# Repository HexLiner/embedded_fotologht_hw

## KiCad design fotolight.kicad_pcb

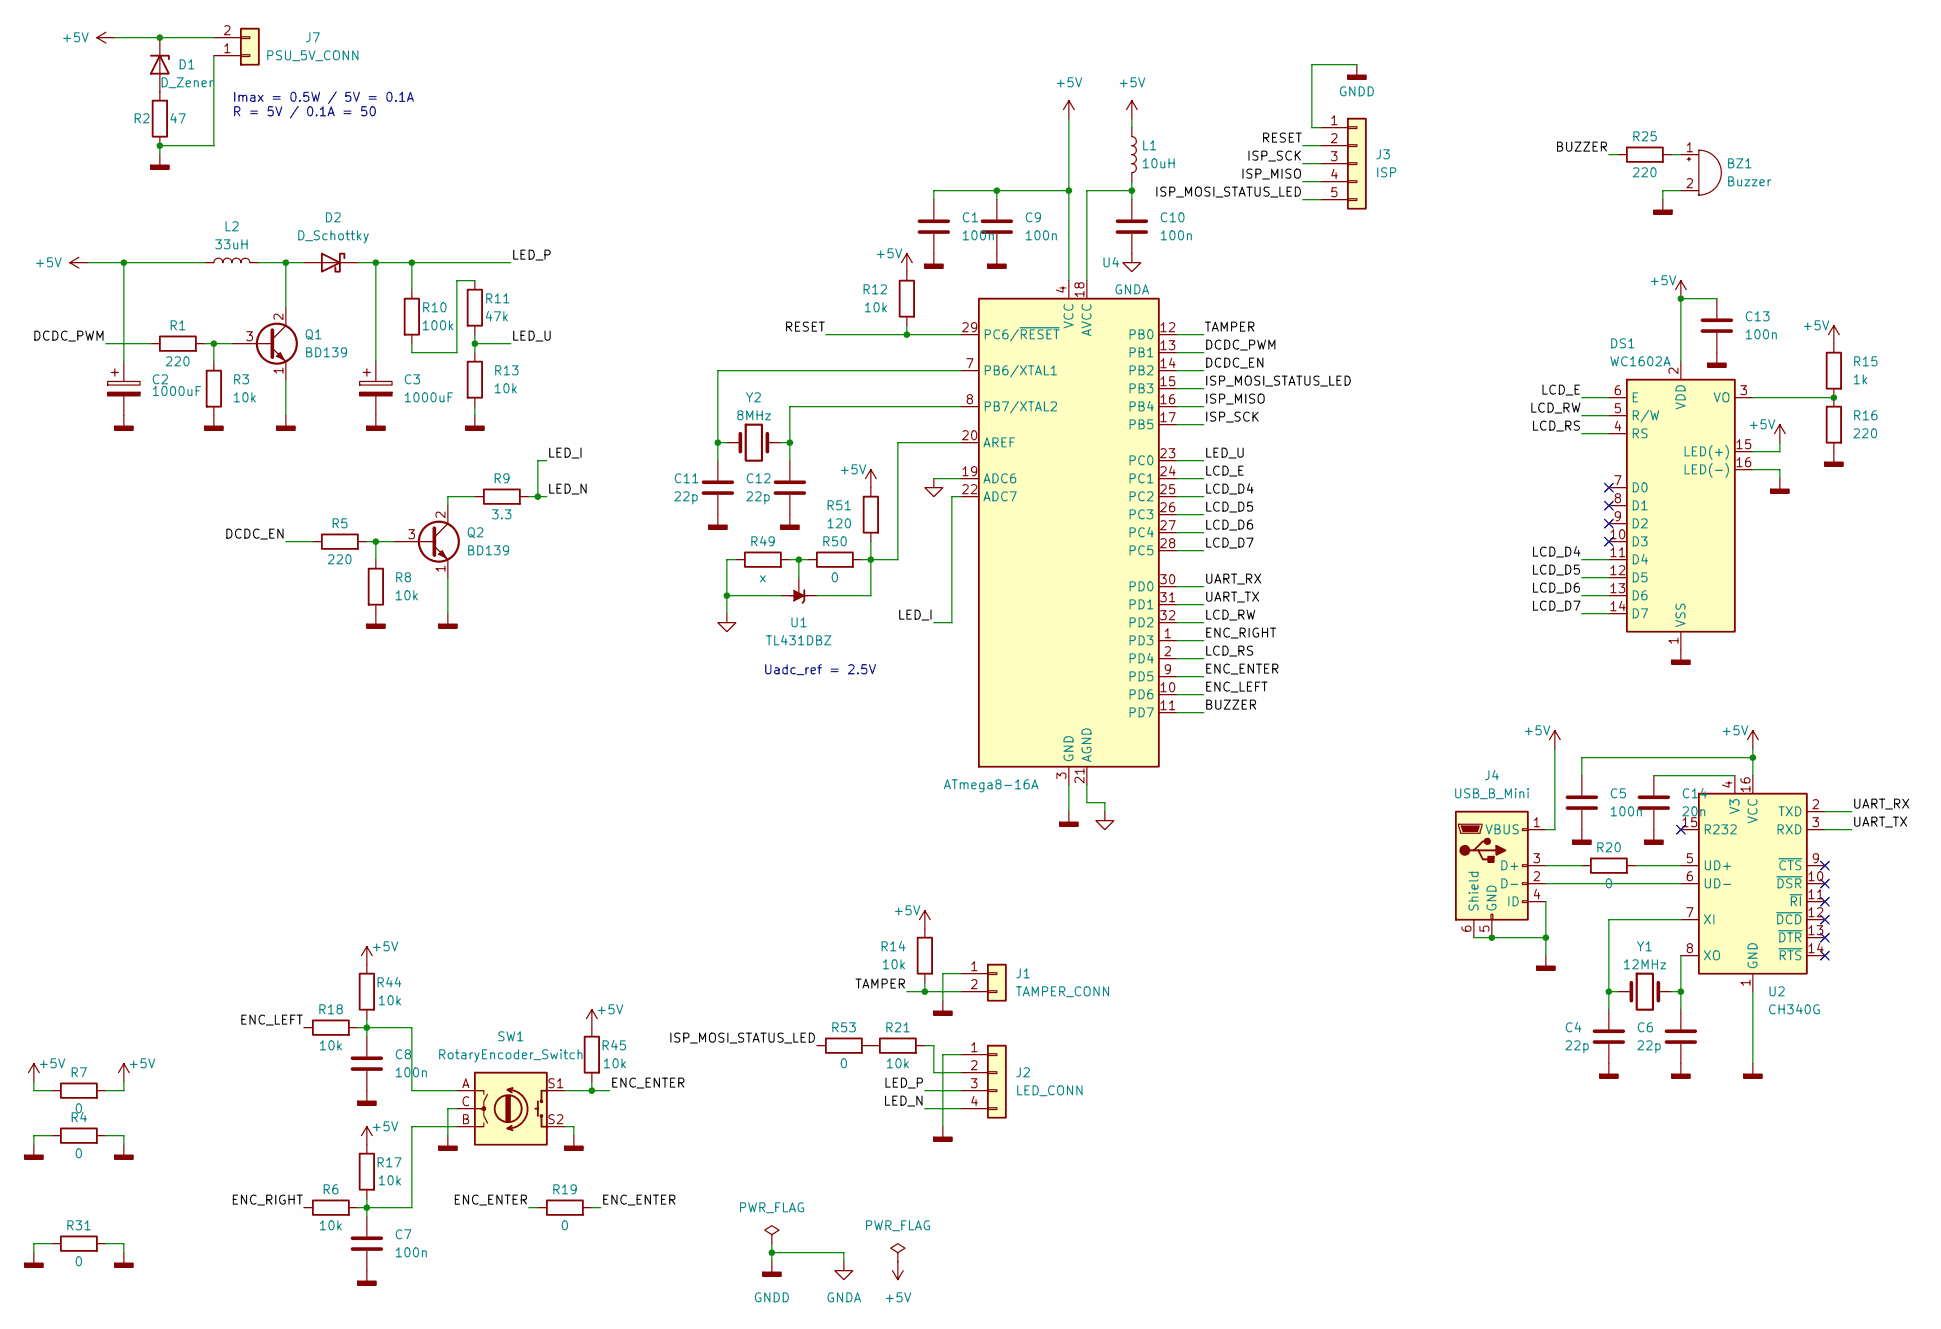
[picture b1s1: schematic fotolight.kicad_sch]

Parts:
BZ1: Buzzer; Buzzer_12x9.5RM7.6
C1, C5, C7, C8, C9, C10, C13: 100n; C_0805_2012Metric
C2, C3: 1000uF; CP_Radial_D5.0mm_P2.50mm
C4, C6, C11, C12: 22p; C_0603_1608Metric
C14: 20n; C_0805_2012Metric
D1: D_Zener; D_SOD-123
D2: D_Schottky; D_SMA
DS1: WC1602A
J1: TAMPER_CONN; PinHeader_1x02_P2.54mm_Horizontal
J2: LED_CONN; PinHeader_1x04_P2.54mm_Horizontal
J3: ISP; PinSocket_1x05_P2.54mm_Vertical
J4: USB_B_Mini; USB_Mini-B_Lumberg_2486_01_Horizontal
J7: PSU_5V_CONN; PinHeader_1x02_P2.54mm_Horizontal
L1: 10uH; L_0805_2012Metric
L2: 33uH; L_12x12mm_H4.5mm
Q1, Q2: BD139; TO-126-3_Vertical
R1, R16, R25: 220; R_0805_2012Metric
R2: 47; R_1206_3216Metric
R3, R8, R12, R13, R45: 10k; R_0805_2012Metric
R4, R7, R19, R20, R31, R53: 0; R_1206_3216Metric
R5: 220; R_1206_3216Metric
R6, R14, R17, R18, R21, R44: 10k; R_1206_3216Metric
R9: 3.3; R_1206_3216Metric
R10: 100k; R_0805_2012Metric
R11: 47k; R_1206_3216Metric
R15: 1k; R_0805_2012Metric
R49: x; R_0805_2012Metric
R50: 0; R_0805_2012Metric
R51: 120; R_0805_2012Metric
SW1: RotaryEncoder_Switch; RotaryEncoder_Alps_EC11E-Switch_Vertical_H20mm
U1: TL431DBZ; SOT-23
U2: CH340G; SOIC-16_3.9x9.9mm_P1.27mm
U4: ATmega8-16A; TQFP-32_7x7mm_P0.8mm
Y1: 12MHz; Crystal_HC18-U_Vertical
Y2: 8MHz; Crystal_HC18-U_Vertical

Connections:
+5V: C1.1, C2.1, C5.1, C9.1, C13.1, D1.1 (K), DS1.2 (VDD), DS1.15 (LED(+)), J4.1 (VBUS), J7.2, L1.1, L2.1, R7.1, R7.2, R12.1, R14.1, R15.1, R17.1, R44.1, R45.1, R51.1, U2.16 (VCC), U4.4 (VCC), U4.6 (VCC)
/BUZZER: R25.1, U4.11 (PD7)
/DCDC_EN: R5.1, U4.14 (PB2)
/DCDC_PWM: R1.1, U4.13 (PB1)
/ENC_ENTER: R19.1, R19.2, R45.2, SW1.S1, U4.9 (PD5)
/ENC_LEFT: R18.1, U4.10 (PD6)
/ENC_RIGHT: R6.1, U4.1 (PD3)
/ISP_MISO: J3.4, U4.16 (PB4)
/ISP_MOSI_STATUS_LED: J3.5, R53.1, U4.15 (PB3)
/ISP_SCK: J3.3, U4.17 (PB5)
/LCD_D4: DS1.11 (D4), U4.25 (PC2)
/LCD_D5: DS1.12 (D5), U4.26 (PC3)
/LCD_D6: DS1.13 (D6), U4.27 (PC4)
/LCD_D7: DS1.14 (D7), U4.28 (PC5)
/LCD_E: DS1.6 (E), U4.24 (PC1)
/LCD_RS: DS1.4 (RS), U4.2 (PD4)
/LCD_RW: DS1.5 (R/W), U4.32 (PD2)
/LED_I: J2.4, R9.2, U4.22 (ADC7)
/LED_P: C3.1, D2.1 (K), J2.3, R10.1
/LED_U: R11.2, R13.1, U4.23 (PC0)
/RESET: J3.2, R12.2, U4.29 (PC6/~RESET)
/TAMPER: J1.2, R14.2, U4.12 (PB0)
/UART_RX: U2.2 (TXD), U4.30 (PD0)
/UART_TX: U2.3 (RXD), U4.31 (PD1)
GNDA: BZ1.2 (+), C1.2, C2.2, C3.2, C4.2, C5.2, C6.2, C7.2, C8.2, C9.2, C10.2, C11.2, C12.2, C13.2, C14.2, DS1.1 (VSS), DS1.16 (LED(-)), J1.1, J2.1, J3.1, J4.4 (ID), J4.5 (GND), J4.6 (Shield), J7.1, Q1.1 (E), Q2.1 (E), R2.1, R3.2, R4.1, R4.2, R8.2, R13.2, R16.2, R31.1, R31.2, R49.1, SW1.C, SW1.S2, U1.3 (A), U2.1 (GND), U4.3 (GND), U4.5 (GND), U4.19 (ADC6), U4.21 (AGND)
unnamed: BZ1.1 (-), R25.2
unnamed: C4.1, U2.7 (XI), Y1.1
unnamed: C6.1, U2.8 (XO), Y1.2
unnamed: C7.1, R6.2, R17.2, SW1.B
unnamed: C8.1, R18.2, R44.2, SW1.A
unnamed: C10.1, L1.2, U4.18 (AVCC)
unnamed: C11.1, U4.7 (PB6/XTAL1), Y2.1
unnamed: C12.1, U4.8 (PB7/XTAL2), Y2.2
unnamed: C14.1, U2.4 (V3)
unnamed: D1.2 (A), R2.2
unnamed: D2.2 (A), L2.2, Q1.2 (C)
unnamed: DS1.3 (VO), R15.2, R16.1
unnamed: J2.2, R21.2
unnamed: J4.2 (D-), U2.6 (UD-)
unnamed: J4.3 (D+), R20.1
unnamed: Q1.3 (B), R1.2, R3.1
unnamed: Q2.2 (C), R9.1
unnamed: Q2.3 (B), R5.2, R8.1
unnamed: R10.2, R11.1
unnamed: R20.2, U2.5 (UD+)
unnamed: R21.1, R53.2
unnamed: R49.2, R50.1, U1.2 (REF)
unnamed: R50.2, R51.2, U1.1 (K), U4.20 (AREF)

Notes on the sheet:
Imax = 0.5W / 5V = 0.1A R = 5V / 0.1A = 50
Uadc_ref = 2.5V

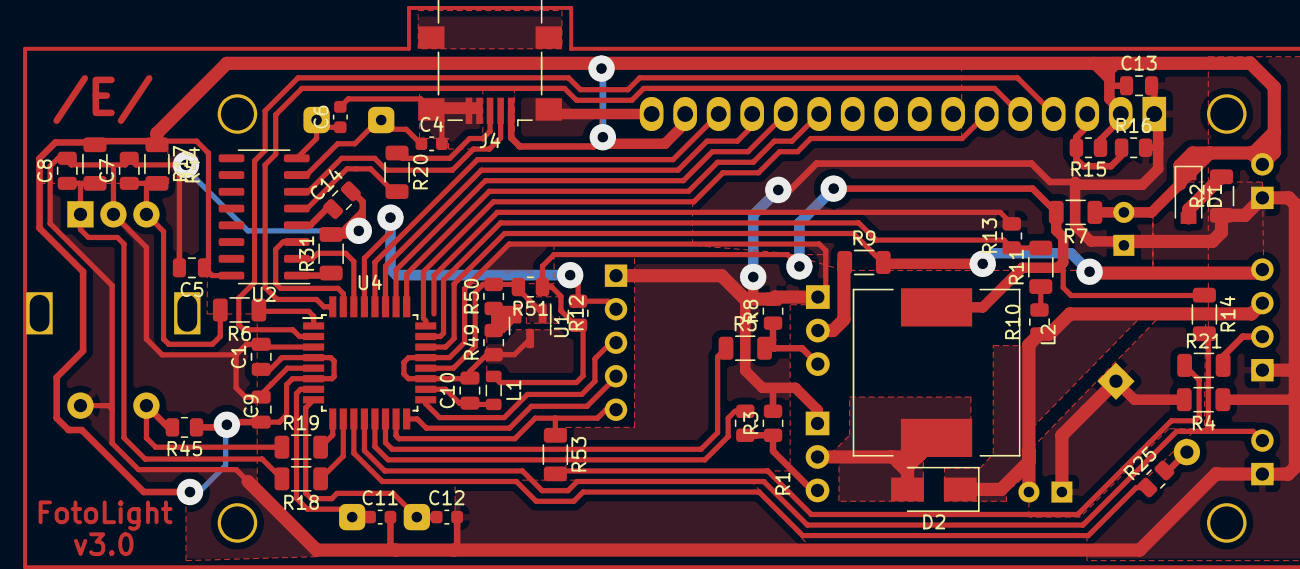
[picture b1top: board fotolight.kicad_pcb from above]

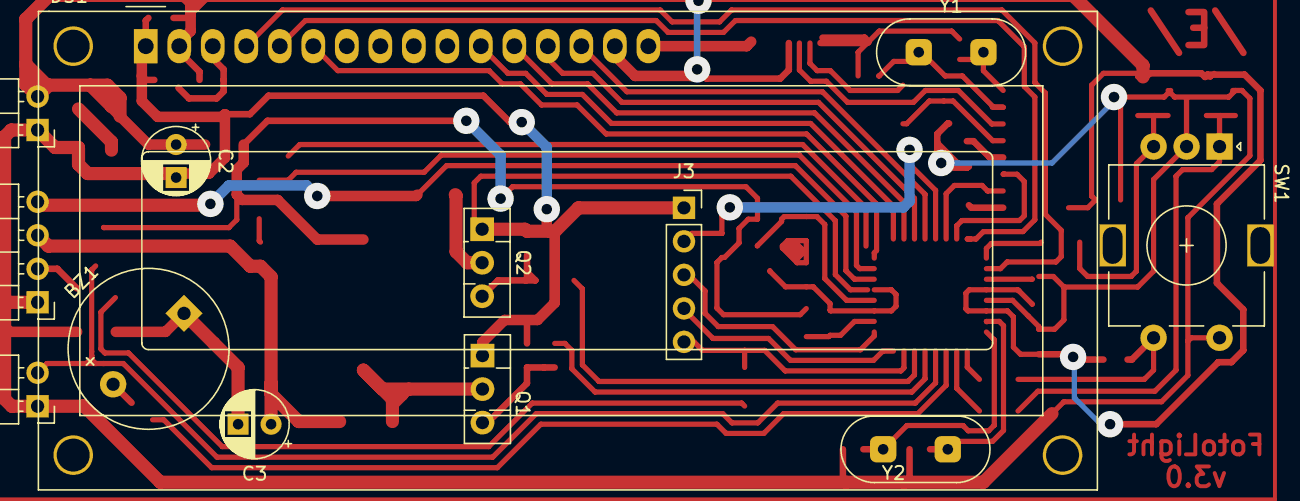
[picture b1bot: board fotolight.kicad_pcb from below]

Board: 2 copper layers, 62 parts (13 on the bottom side), 48 nets.

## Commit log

2025-03-05 Initial
